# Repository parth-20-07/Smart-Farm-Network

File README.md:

<!-- omit from toc -->
# Smart Farm Network

**Table of Contents**

- [Introduction](#introduction)
- [Sensor Node](#sensor-node)
  - [Hardware Components](#hardware-components)
  - [Schematic](#schematic)
  - [PCB Design](#pcb-design)
- [Server Functionality](#server-functionality)
  - [Core Functions](#core-functions)
- [Setup and Operation](#setup-and-operation)
- [Data Handling and Alerts](#data-handling-and-alerts)
- [Customization and Expansion](#customization-and-expansion)
- [License](#license)
- [Design Details](#design-details)

# Introduction
The Smart Farm Network is a cutting-edge agricultural monitoring system designed to provide real-time insights into environmental conditions. Using a network of sensor nodes and a central server, it delivers detailed data analysis to help manage and optimize farming operations.

# Sensor Node
Equipped with sensors for temperature, humidity, lux, and CO2, each node collects data at set intervals. An integrated RTC ensures accurate timestamping. The nodes communicate with the server using BLE technology.

## Hardware Components
- **MicroUSB for Charging:** Ensures easy and accessible charging.
- **Battery Management:** Monitors and manages battery levels.
- **Power Conversion Units:** Provide the necessary voltages for different components.
- **ESP32 WROOM Module:** Processes and transmits the sensor data.
- **MicroSD Card Slot:** Enables data logging and storage.

## Schematic

## PCB Design

**PCB Top View**

**PCB Bottom View**

# Server Functionality
The server firmware manages data from over 50 nodes, calculating averages, and issuing alerts if readings exceed thresholds. It features:

## Core Functions
- **Data Processing:** Analyzes incoming data and manages MQTT connections to Digital Ocean for cloud uploads.
- **Display Control:** Updates the HMI display with real-time data and alert statuses.
- **Configuration Management:** Offers a web server interface for device configuration.
- **OTA Updates:** Maintains system integrity with the latest firmware updates.

# Setup and Operation
1. **Assembling Sensor Nodes:** Follow the provided schematics to assemble the hardware.
2. **Installing Firmware:** Flash the sensor nodes and server with the respective firmware.
3. **Configuring the Network:** Connect the nodes to the server via BLE and set up the server's Wi-Fi and MQTT settings.
4. **Launching the System:** Power up the system, and it begins automatic data collection and analysis.

# Data Handling and Alerts
The system stores data in microSD cards and uploads it to the cloud. It calculates average values and displays alerts on the HMI screen if parameters exceed set thresholds.

# Customization and Expansion
The firmware's modular design allows for easy addition of new sensors or communication protocols.

# License
This project is licensed under the GNU General Public License v3.0. See [LICENSE.md](LICENSE.md) for details.

# Design Details

- Designed for: City Green Private Ltd.
- Designed by: [Parth Patel](mailto:parth.pmech@gmail.com)

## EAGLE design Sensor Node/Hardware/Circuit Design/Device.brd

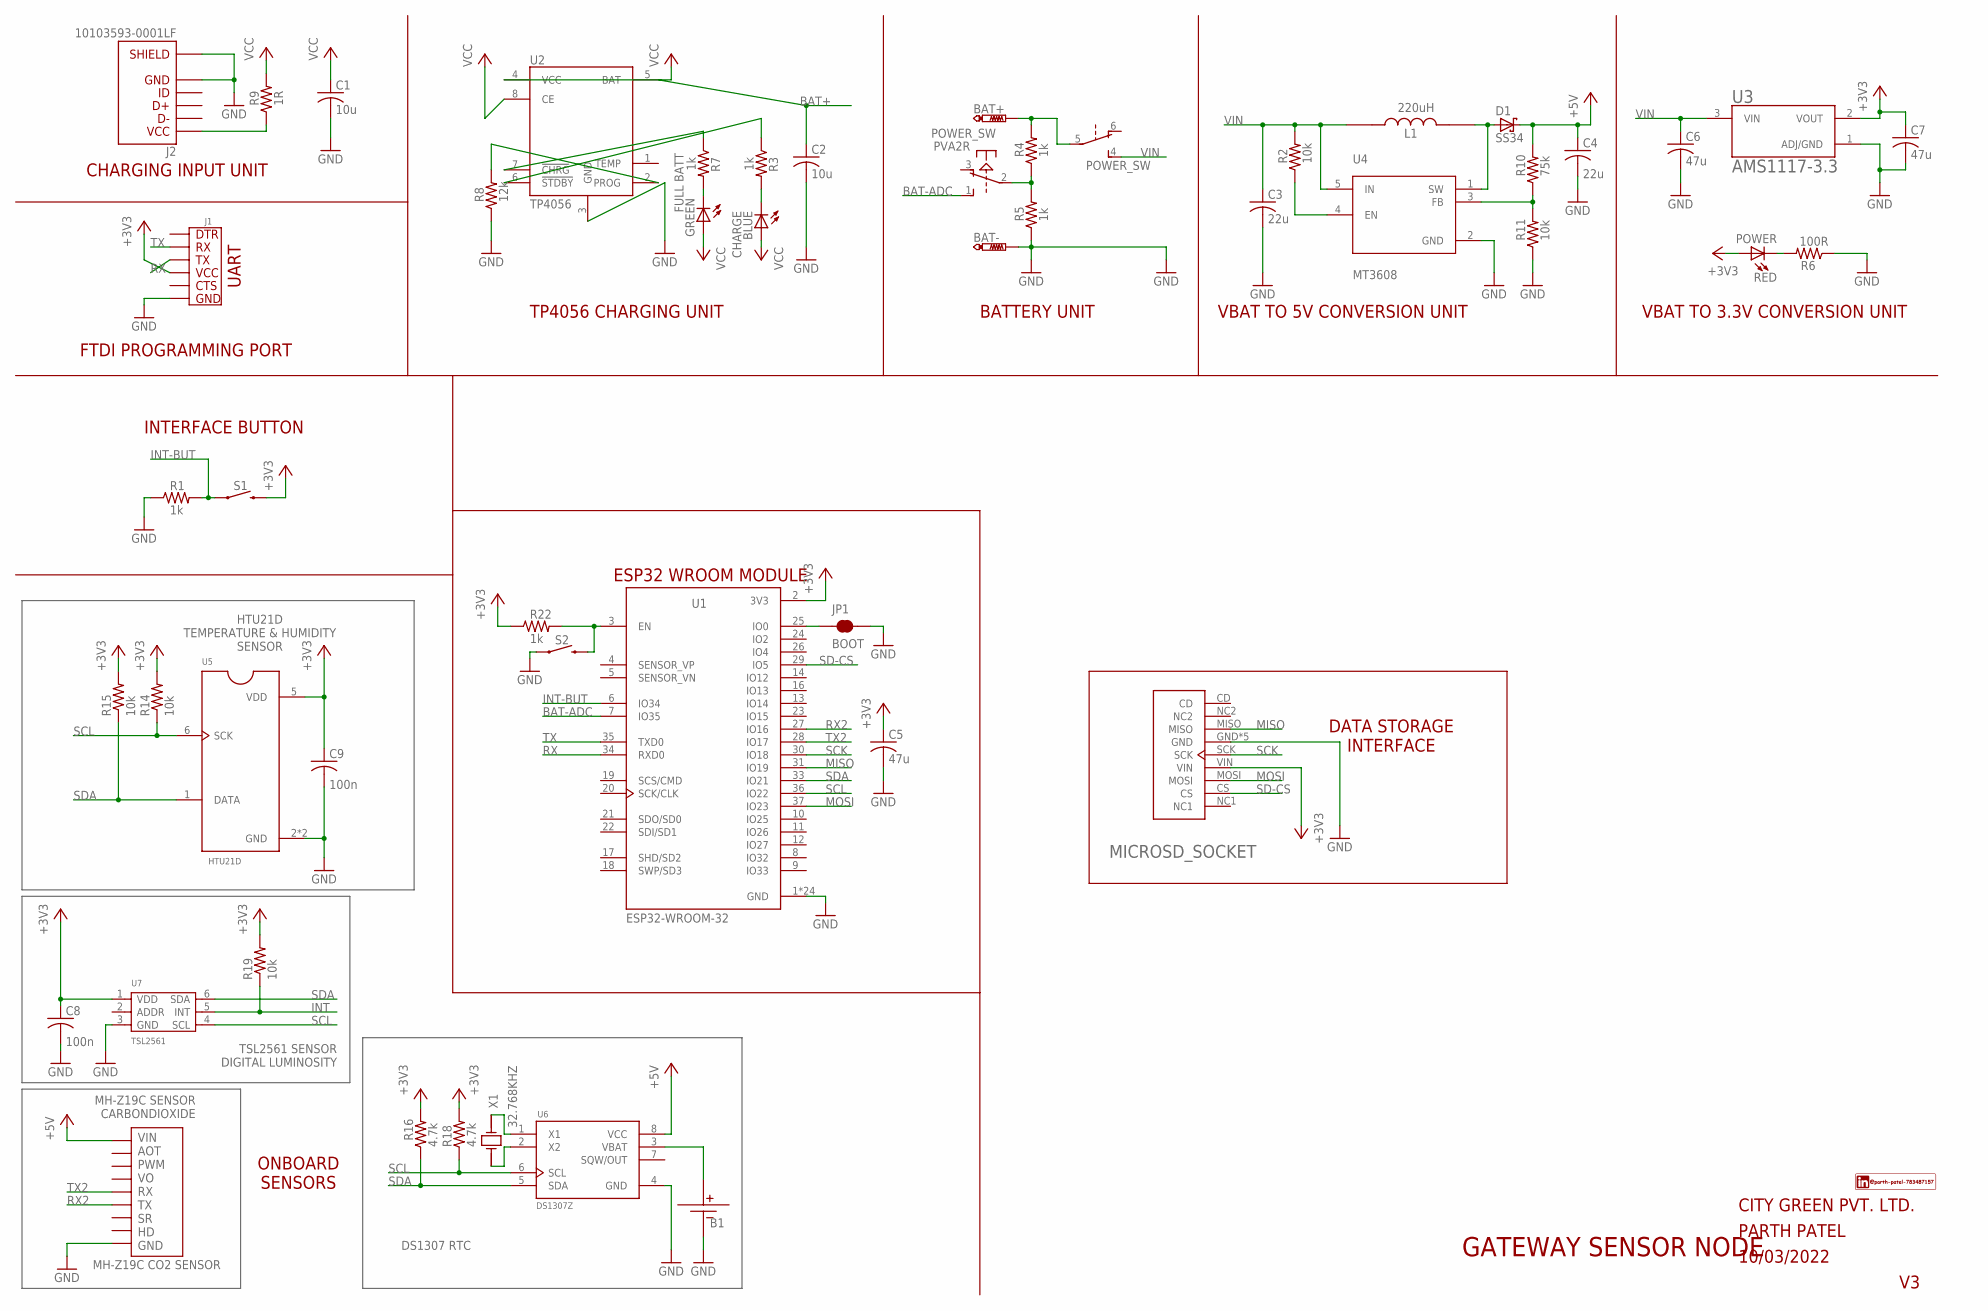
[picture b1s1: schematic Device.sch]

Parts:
B1: CR3032-METAL; CR2032-METAL
BAT+: PTR1TP20SQ; TP20SQ
BAT-: PTR1TP20SQ; TP20SQ
BLUE: CHARGE; CHIP-LED0603
C1, C2: 10u; C0805
C3, C4: 22u; C0805
C5, C6, C7: 47u; C0805
C8, C9: 100n; C0805
D1: SS34; DO214
GREEN: FULL BATT; CHIP-LED0603
J1: UART
J2: 10103593-0001LF; AMPHENOL_10103593-0001LF
JP1: BOOT; SMT-JUMPER_2_NC_TRACE_NO-SILK
L1: 220uH; IND_#B953AS-221M=P3
MICROSD_SOCKET: ST-TF-003A; SUNTECH_ST-TF-003A
POWER_SW: PVA2R
R1, R3, R4, R5, R7, R22: 1k; R0805
R2, R11, R14, R15, R19: 10k; R0805
R6: 100R; R0805
R8: 12k; R0805
R9: 1R; R0805
R10: 75k; R0805
R16, R18: 4.7k; R0805
RED: POWER; CHIP-LED0603
S1: MOMENTARY-SWITCH-SPST-SMD-6.2MM-TALL; TACTILE_SWITCH_SMD_6.2MM_TALL
S2: RST; TACTILE_SWITCH_SMD_6.2MM_TALL
U1: ESP32-WROOM-32; MODULE_ESP32-WROOM-32
U2: TP4056; SOP127P600X175-9N
U3: AMS1117-3.3; SOT229P700X180-4N
U4: MT3608; SOT95P280X145-6N
U5: HTU21D; QFN100P300X300X100-7N
U6: DS1307Z; SOIC127P600X175-8N
U7: TSL2561; TMB6-1.55-3.8X2.6MM
U$1: MH-Z19C
X1: 32.768KHZ; XTAL_AB38T-32.768KHZ

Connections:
+3V3: C5.1, C7.1, C8.1, C9.1, J1.VCC, MICROSD_SOCKET.VIN, R14.2, R15.2, R16.2, R18.2, R19.2, R22.1, RED.A, S1.B2 (2), U1.2 (3V3), U3.2 (VOUT), U5.5 (VDD), U7.1 (VDD)
+5V: C4.1, D1.C, R10.2, U6.8 (VCC), U$1.VIN
BAT+: BAT+.TP, C2.1, POWER_SW.5, R4.2, U2.5 (BAT)
BAT-ADC: POWER_SW.1 (S), U1.7 (IO35)
BAT-ADC-IN: POWER_SW.2, R4.1, R5.2
GND: B1.-VE1 (-VE), B1.-VE2 (-VE), BAT-.TP, C1.2, C2.2, C3.2, C4.2, C5.2, C6.2, C7.2, C8.2, C9.2, J1.GND, J2.5, J2.S1 (SHIELD), J2.S2 (SHIELD), J2.S3 (SHIELD), J2.S4 (SHIELD), J2.S5 (SHIELD), J2.S6 (SHIELD), JP1.2, MICROSD_SOCKET.GND, MICROSD_SOCKET.GND2 (GND), MICROSD_SOCKET.GND3 (GND), MICROSD_SOCKET.GND4 (GND), MICROSD_SOCKET.GND5 (GND), R1.1, R5.1, R6.1, R8.1, R11.1, S2.A2 (1), U1.1 (GND), U1.15 (GND), U1.38 (GND), U1.39_1 (GND), U1.39_2 (GND), U1.39_3 (GND), U1.39_4 (GND), U1.39_5 (GND), U1.39_6 (GND), U1.39_7 (GND), U1.39_8 (GND), U1.39_9 (GND), U1.39_10 (GND), U1.39_11 (GND), U1.39_12 (GND), U1.39_13 (GND), U1.39_14 (GND), U1.39_15 (GND), U1.39_16 (GND), U1.39_17 (GND), U1.39_18 (GND), U1.39_19 (GND), U1.39_20 (GND), U1.39_21 (GND), U2.3 (GND), U3.1 (ADJ/GND), U4.2 (GND), U5.2 (GND), U5.PAD (GND), U6.4 (GND), U7.3 (GND), U$1.GND
INT: R19.1, U7.5 (INT)
INT-BUT: R1.2, S1.A2 (1), U1.6 (IO34)
MISO: MICROSD_SOCKET.MISO, U1.31 (IO19)
MOSI: MICROSD_SOCKET.MOSI, U1.37 (IO23)
unnamed: R8.2, U2.2 (PROG)
unnamed: R6.2, RED.C
unnamed: J2.1, R9.1
unnamed: B1.+VE, U6.3 (VBAT)
unnamed: R2.1, U4.4 (EN)
unnamed: R3.1, U2.6 (!STDBY)
unnamed: R7.1, U2.7 (!CHRG)
unnamed: BLUE.C, R3.2
unnamed: GREEN.C, R7.2
unnamed: D1.A, L1.2, U4.1 (SW)
unnamed: R10.1, R11.2, U4.3 (FB)
unnamed: JP1.1, U1.25 (IO0)
unnamed: U6.2 (X2), X1.1
unnamed: R22.2, S2.B2 (2), U1.3 (EN)
unnamed: U6.1 (X1), X1.2
RX: J1.TX, U1.34 (RXD0)
RX2: U1.27 (IO16), U$1.TX
SCK: MICROSD_SOCKET.SCK, U1.30 (IO18)
SCL: R14.1, R18.1, U1.36 (IO22), U5.6 (SCK), U6.6 (SCL), U7.4 (SCL)
SD-CS: MICROSD_SOCKET.CS, U1.29 (IO5)
SDA: R15.1, R16.1, U1.33 (IO21), U5.1 (DATA), U6.5 (SDA), U7.6 (SDA)
TX: J1.RX, U1.35 (TXD0)
TX2: U1.28 (IO17), U$1.RX
VCC: BLUE.A, C1.1, GREEN.A, R9.2, U2.4 (VCC), U2.8 (CE)
VIN: C3.1, C6.1, L1.1, POWER_SW.4 (S), R2.2, U3.3 (VIN), U4.5 (IN)

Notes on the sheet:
ESP32 WROOM MODULE
MH-Z19C SENSOR CARBONDIOXIDE
TSL2561 SENSOR DIGITAL LUMINOSITY
ONBOARD SENSORS
INTERFACE BUTTON
DATA STORAGE INTERFACE
GATEWAY SENSOR NODE
CITY GREEN PVT. LTD.
PARTH PATEL
10/03/2022
TP4056 CHARGING UNIT
BATTERY UNIT
CHARGING INPUT UNIT
VBAT TO 5V CONVERSION UNIT
VBAT TO 3.3V CONVERSION UNIT
HTU21D TEMPERATURE & HUMIDITY SENSOR
DS1307 RTC
FTDI PROGRAMMING PORT

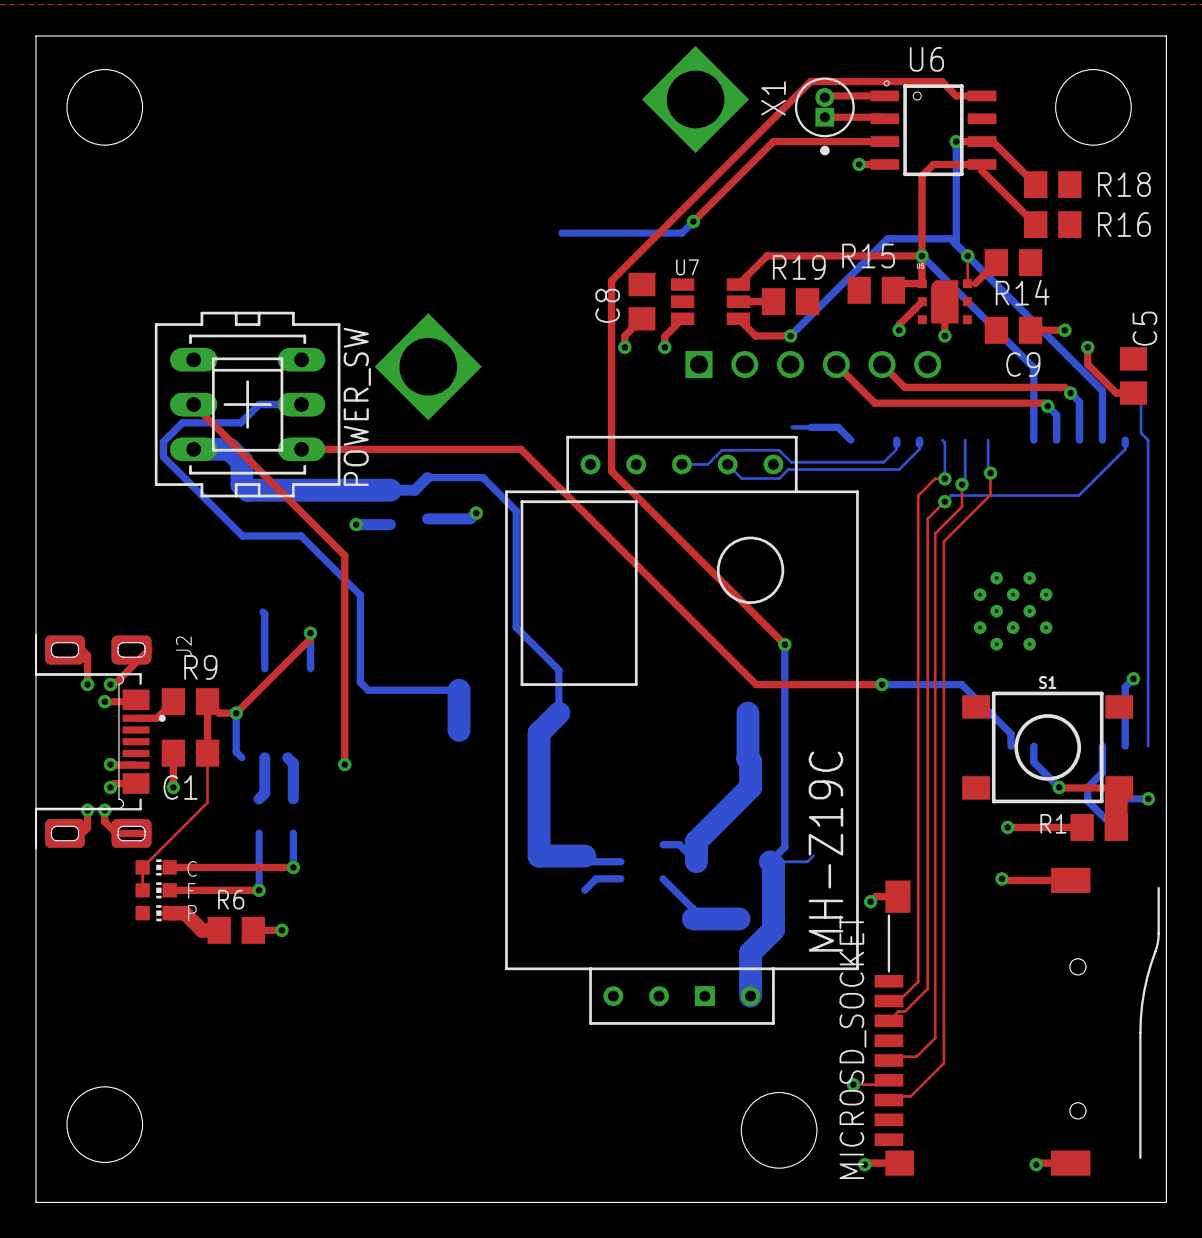
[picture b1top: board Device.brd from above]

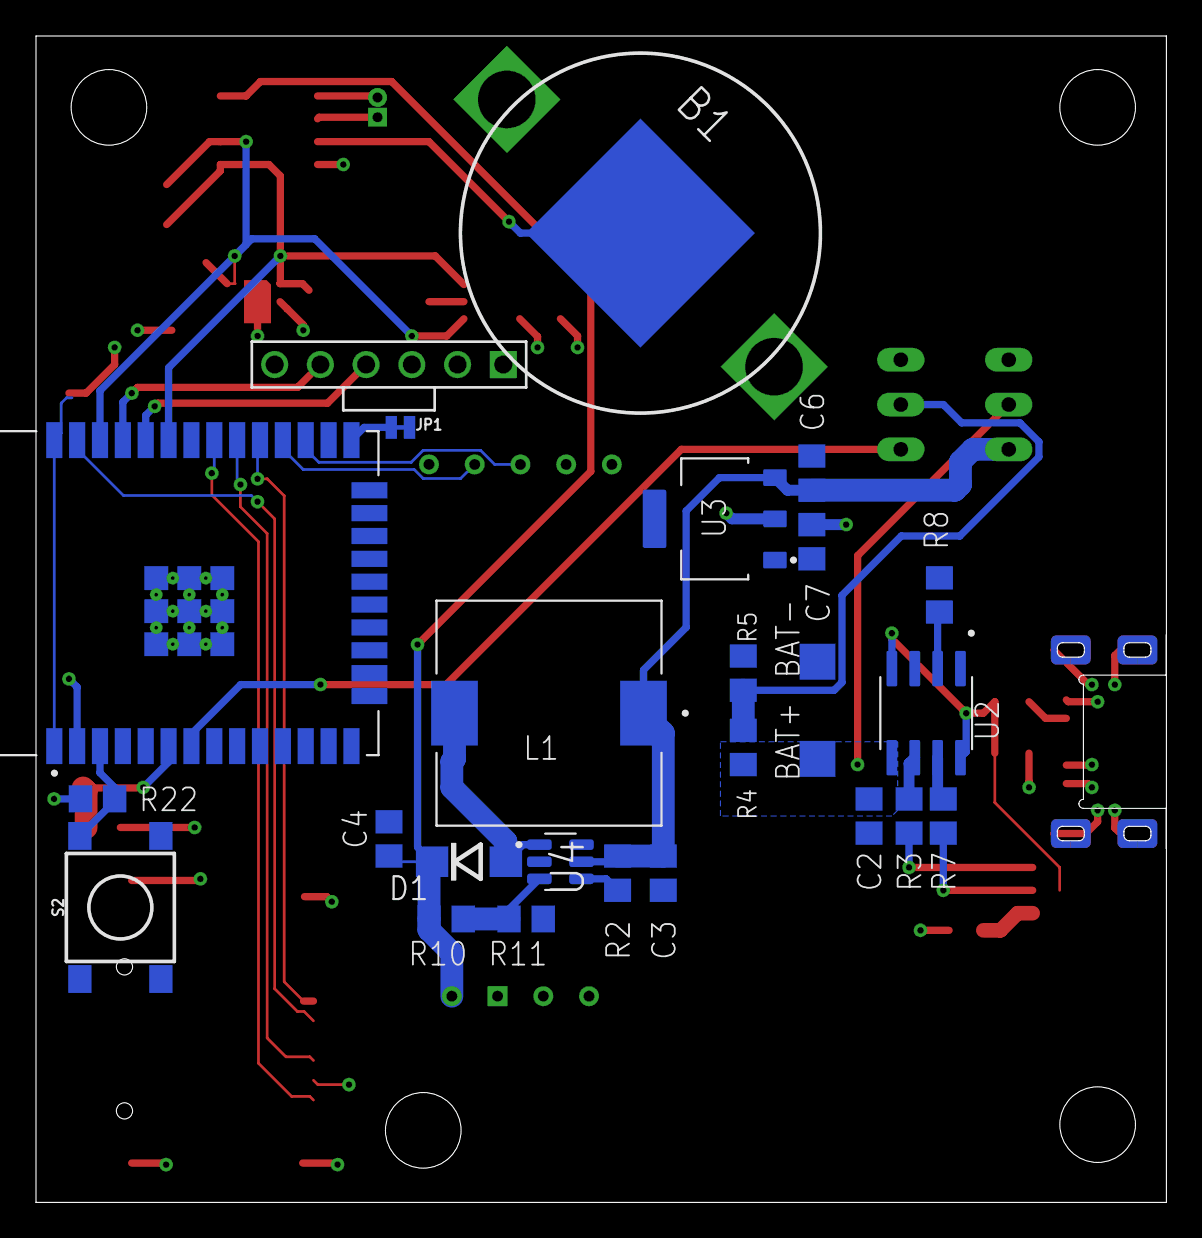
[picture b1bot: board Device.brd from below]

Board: 2 copper layers, 62.8 x 64.8 mm, 50 parts (26 on the bottom side), 35 nets.

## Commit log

2022-12-24 Upload project files to github
2023-12-18 Update TOC

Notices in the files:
parts and their libraries:
SparkFun-Switches: Licensing: Creative Commons ShareAlike 4.0 International - https://creativecommons.org/licenses/by-sa/4.0
